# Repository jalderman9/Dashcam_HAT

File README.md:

# Dashcam HAT

This repository contains the Eagle PCB design files for a board that
attaches to an ASUS Tinkerboard and provides:
 - Regulated 5V power from OBD-II 12V supply
 - Power management via Attiny
 - OBD-II interface (CAN and ISO9141)
 - 3 axis accelerometer
 - magnetometer
 - GPS

PCB top view:

PCB bottom view:

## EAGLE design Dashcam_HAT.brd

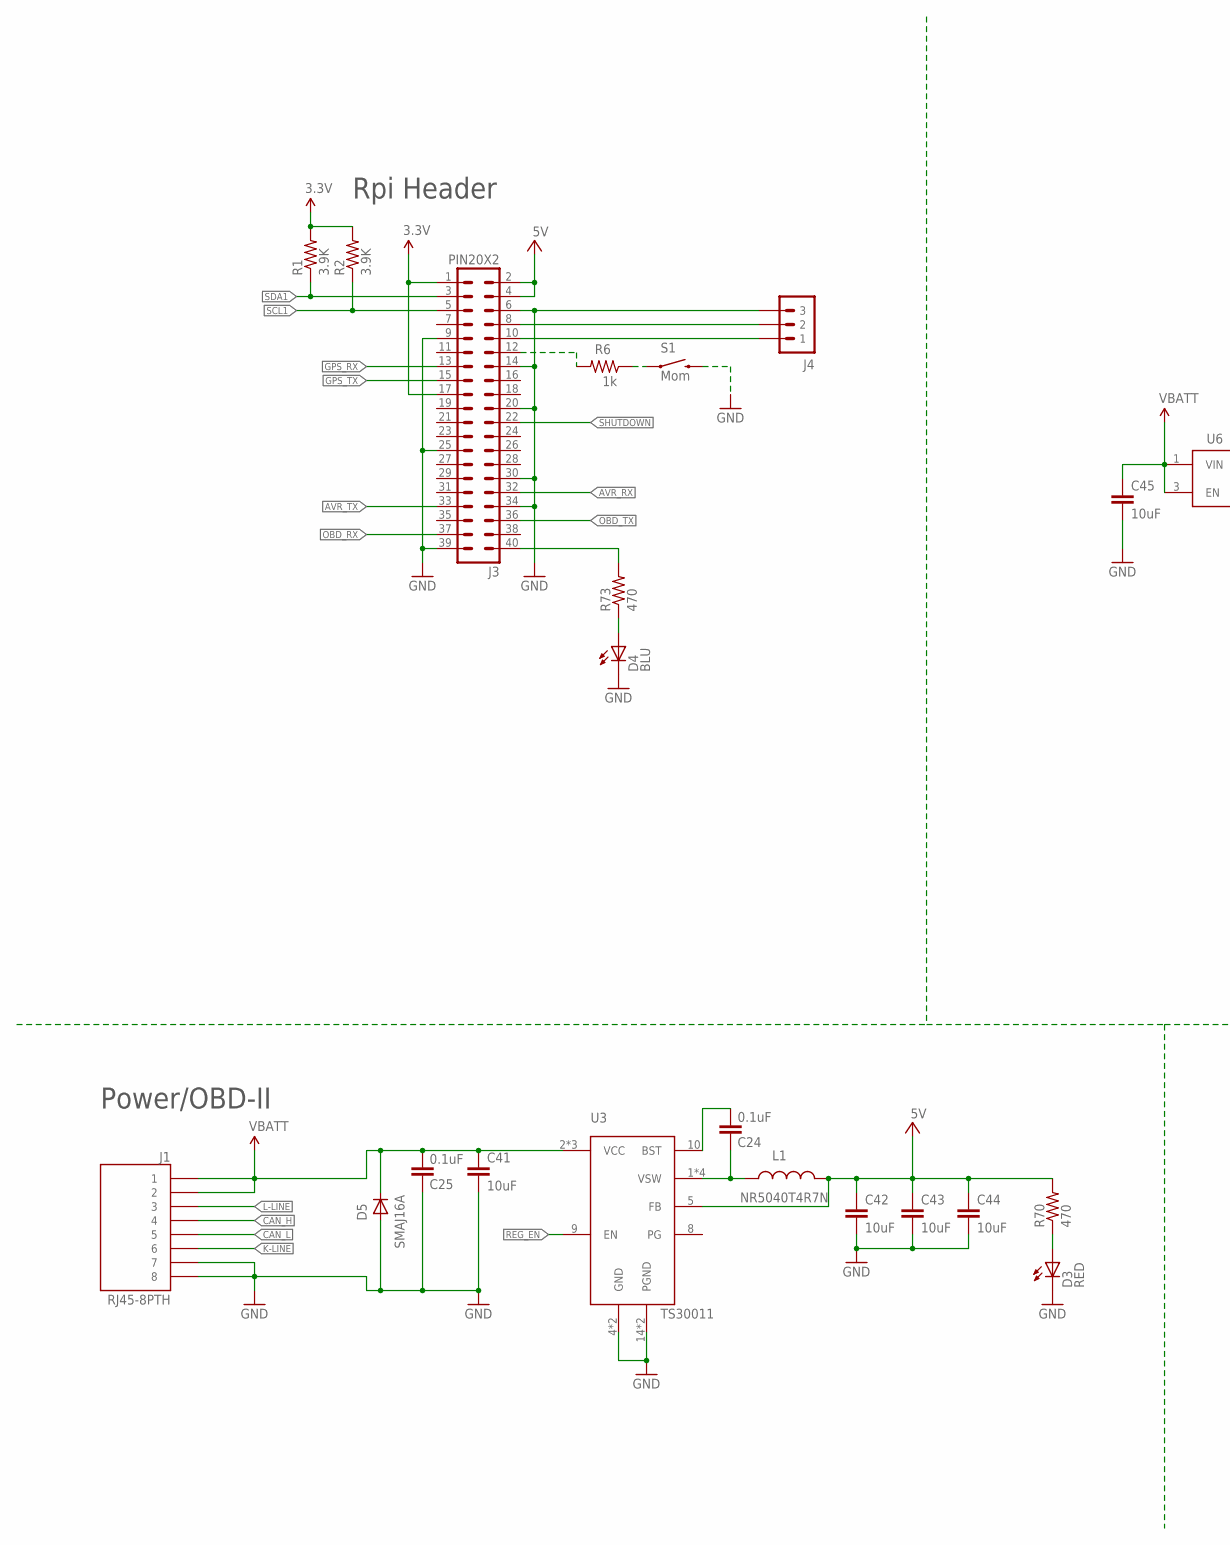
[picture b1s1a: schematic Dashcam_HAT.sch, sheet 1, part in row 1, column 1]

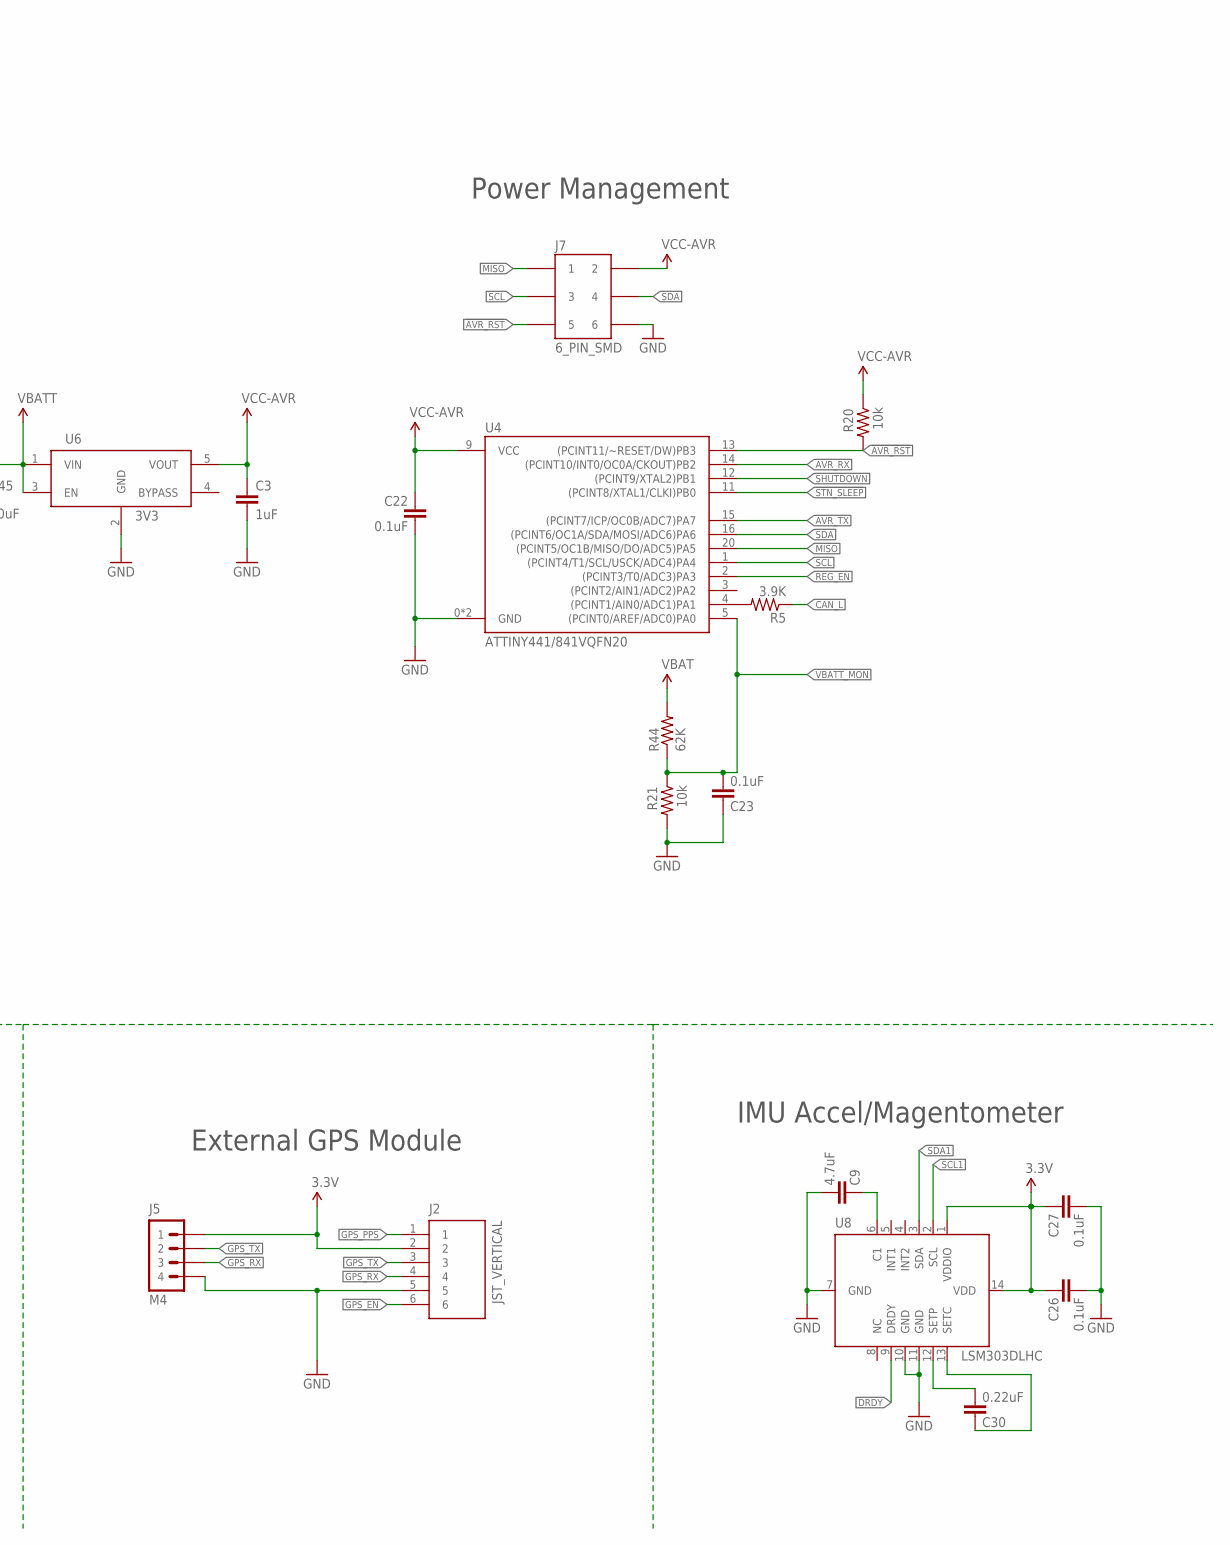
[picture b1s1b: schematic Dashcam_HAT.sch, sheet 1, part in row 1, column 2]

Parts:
C3: 1uF; 0402-CAP; MFG_PN GRM155R61A105KE15D; DIGIKEY_PN 490-3890-1-ND
C9: 4.7uF; 0402-CAP; MFG_PN GRM155R60J475ME47D; DIGIKEY_PN 490-5915-1-ND
C22, C23, C24, C25, C26, C27: 0.1uF; 0402-CAP; MFG_PN CL05B104KO5NNNC; DIGIKEY_PN 1276-1001-1-ND
C30: 0.22uF; 0402-CAP; MFG_PN GRM155R71C224KA12D; DIGIKEY_PN 490-5418-1-ND
C41, C42, C43, C44, C45: 10uF; 1206; MFG_PN CL31B106KBHNNNE; DIGIKEY_PN 1276-6767-1-ND
D3: RED; LED_0603; MFG_PN LTST-C190KRKT; DIGIKEY_PN 160-1436-1-ND
D4: BLU; LED_0603; MFG_PN LTST-C190TBKT; DIGIKEY_PN 160-1646-1-ND
D5: SMAJ16A; SMA; MFG_PN SMAJ16A; DIGIKEY_PN SMAJ16ALFCT-ND
J1: RJ45-8PTH; RJ45-8; MFG_PN 54602-908LF; DIGIKEY_PN 609-1046-ND
J2: JST_VERTICAL; JST-6-SMD-VERT-1.0MM; MFG_PN BM06B-SRSS-TB(LF)(SN); DIGIKEY_PN 455-1792-1-ND
J3: PIN20X2; PIN_20X2; MFG_PN ESQ-120-23-T-D; DIGIKEY_PN SAM9315-ND
J4: M30.1"_LOCK; M3X1_LOCK
J5: M4; M4X1_LOCK
J7: 6_PIN_SMD; M3X2_SMD; MFG_PN 20021121-00006C4LF; DIGIKEY_PN 609-3693-1-ND
L1: NR5040T4R7N; NR5040; MFG_PN 587-2373-1-ND; DIGIKEY_PN 587-2373-1-ND
R1, R2, R5: 3.9K; 0402-RES; MFG_PN RC0402JR-073K9L; DIGIKEY_PN 311-3.9KJRCT-ND
R6: 1k; 0402-RES; MFG_PN RC0402JR-071KL; DIGIKEY_PN 311-1.0KJRCT-ND
R20, R21: 10k; 0402-RES; MFG_PN RC0402JR-0710KL; DIGIKEY_PN 311-10KJRCT-ND
R44: 62K; 0402-RES; MFG_PN RC0402FR-0762KL; DIGIKEY_PN 311-62.0KLRCT-ND
R70, R73: 470; 0603-RES; MFG_PN RC0402JR-07470RL; DIGIKEY_PN 311-470JRCT-ND
S1: Mom; TACTILE-SWITCH-1101NE; MFG_PN EVQ-PNF04M; DIGIKEY_PN P13597SCT-ND
U3: TS30011; QFN-16; MFG_PN TS30013-M050QFNR; DIGIKEY_PN TS30013-M050QFNRCT-ND
U4: ATTINY441/841VQFN20; QFN20_0.45MM; MFG_PN ATTINY841-MMH; DIGIKEY_PN ATTINY841-MMH-ND
U6: 3V3; SOT23-5; MFG_PN AP2204K-3.3TRG1; DIGIKEY_PN AP2204K-3.3TRG1DICT-ND
U8: LSM303DLHC; LGA14; MFG_PN LSM303DLHCTR; DIGIKEY_PN 497-11918-1-ND

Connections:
3.3V: C26.1, C27.1, J2.2, J3.1, J3.17, J5.1, R1.2, R2.2, U8.1 (VDDIO), U8.14 (VDD); also elsewhere on the board
5V: C42.1, C43.1, C44.1, J3.2, J3.4, L1.P$2 (2), R70.2, U3.5 (FB); also elsewhere on the board
!AVR_RST: J7.P$5 (5), R20.2, U4.13 ((PCINT11/~RESET/DW)PB3)
!STN_SLEEP: U4.11 ((PCINT8/XTAL1/CLKI)PB0); also elsewhere on the board
AVR_RX: J3.32, U4.14 ((PCINT10/INT0/OC0A/CKOUT)PB2)
AVR_TX: J3.33, U4.15 ((PCINT7/ICP/OC0B/ADC7)PA7)
BST: C24.2, U3.10 (BST)
CAN_H: J1.4; also elsewhere on the board
CAN_L: J1.5, R5.1; also elsewhere on the board
DRDY: U8.9 (DRDY)
GND: C3.2, C9.2, C22.2, C23.1, C25.1, C26.2, C27.2, C41.2, C42.2, C43.2, C44.2, C45.2, D3.C, D4.C, D5.A, J1.7, J1.8, J2.5, J3.6, J3.9, J3.14, J3.20, J3.25, J3.30, J3.34, J3.39, J4.3, J5.4, J7.P$6 (6), R21.2, S1.P$2 (2), U3.4 (GND), U3.14 (PGND), U3.15 (PGND), U3.EXP (GND), U4.0 (GND), U4.8 (GND), U6.2 (GND), U8.7 (GND), U8.10 (GND), U8.11 (GND); also elsewhere on the board
GPS_EN: J2.6
GPS_PPS: J2.1
GPS_RX: J2.4, J3.13, J5.3
GPS_TX: J2.3, J3.15, J5.2
K-LINE: J1.6; also elsewhere on the board
L-LINE: J1.3; also elsewhere on the board
MISO: J7.P$1 (1), U4.20 ((PCINT5/OC1B/MISO/DO/ADC5)PA5)
unnamed: C9.1, U8.6 (C1)
unnamed: R5.2, U4.4 ((PCINT1/AIN0/ADC1)PA1)
unnamed: D3.A, R70.1
unnamed: D4.A, R73.1
unnamed: C30.2, U8.12 (SETP)
unnamed: C30.1, U8.13 (SETC)
unnamed: J3.12, R6.2
unnamed: R6.1, S1.P$1 (1)
OBD_RX: J3.37; also elsewhere on the board
OBD_TX: J3.36; also elsewhere on the board
REG_EN: U3.9 (EN), U4.2 ((PCINT3/T0/ADC3)PA3)
SCL: J7.P$3 (3), U4.1 ((PCINT4/T1/SCL/USCK/ADC4)PA4)
SCL1: J3.5, R2.1, U8.2 (SCL)
SDA: J7.P$4 (4), U4.16 ((PCINT6/OC1A/SDA/MOSI/ADC6)PA6)
SDA1: J3.3, R1.1, U8.3 (SDA)
SHUTDOWN: J3.22, U4.12 ((PCINT9/XTAL2)PB1)
UART1_RX: J3.10, J4.1
UART1_TX: J3.8, J4.2
USER_LED: J3.40, R73.2
VBATT: C25.2, C41.1, C45.1, D5.K (C), J1.1, J1.2, R44.2, U3.2 (VCC), U3.3 (VCC), U3.11 (VCC), U6.1 (VIN), U6.3 (EN); also elsewhere on the board
VBATT_MON: C23.2, R21.1, R44.1, U4.5 ((PCINT0/AREF/ADC0)PA0)
VCC-AVR: C3.1, C22.1, J7.P$2 (2), R20.1, U4.9 (VCC), U6.5 (VOUT)
VSW: C24.1, L1.P$1 (1), U3.1 (VSW), U3.12 (VSW), U3.13 (VSW), U3.16 (VSW)

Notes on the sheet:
External GPS Module
Rpi Header
IMU Accel/Magentometer
Power/OBD-II
Power Management

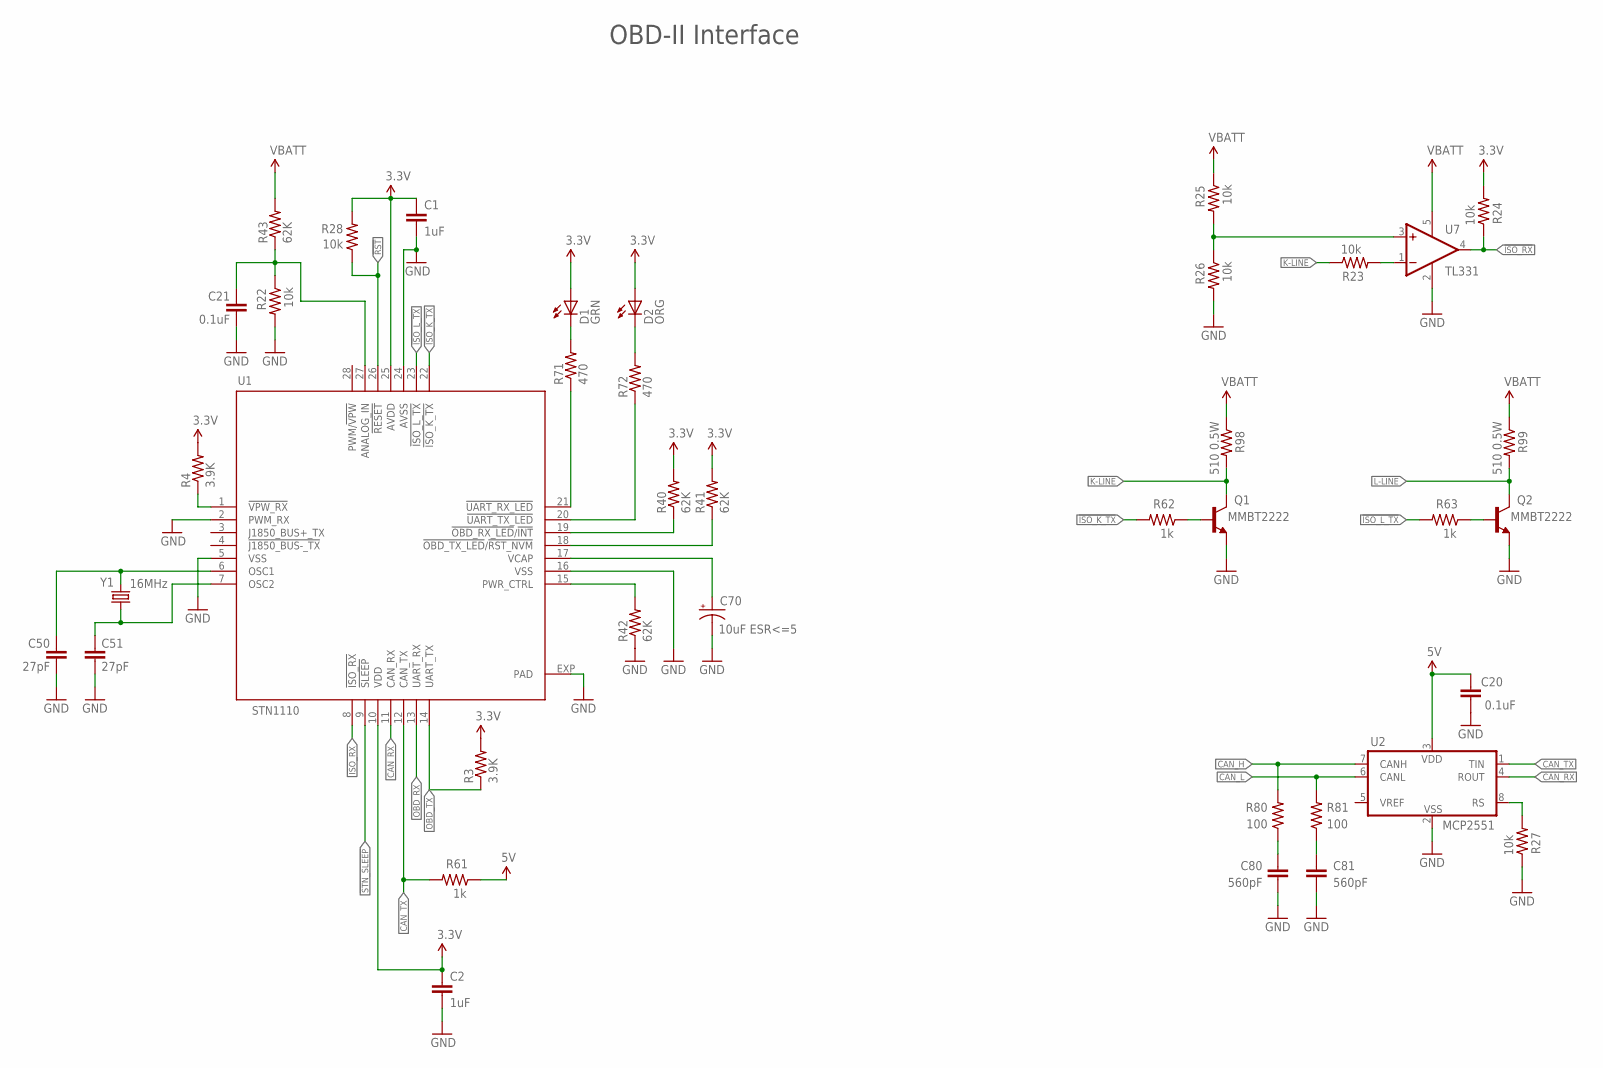
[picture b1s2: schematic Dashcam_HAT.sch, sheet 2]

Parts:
C1, C2: 1uF; 0402-CAP; MFG_PN GRM155R61A105KE15D; DIGIKEY_PN 490-3890-1-ND
C20, C21: 0.1uF; 0402-CAP; MFG_PN CL05B104KO5NNNC; DIGIKEY_PN 1276-1001-1-ND
C50: 27pF; 0402-CAP; MFG_PN CL05C270JB5NNNC; DIGIKEY_PN 1276-1153-1-ND
C51: 27pF; 0402-CAP
C70: 10uF ESR<=5; EIA3216; MFG_PN F931C106MAA; DIGIKEY_PN 478-8237-1-ND
C80, C81: 560pF; 0402-CAP; MFG_PN CL05B561KB5NNNC; DIGIKEY_PN 1276-1577-1-ND
D1: GRN; LED_0603; MFG_PN LTST-C190GKT; DIGIKEY_PN 160-1183-1-ND
D2: ORG; LED_0603; MFG_PN LTST-C190KFKT; DIGIKEY_PN 160-1434-1-ND
Q1, Q2: MMBT2222; SOT23-3; MFG_PN MMBT2222ALT1G; DIGIKEY_PN MMBT2222ALT1GOSCT-ND
R3, R4: 3.9K; 0402-RES; MFG_PN RC0402JR-073K9L; DIGIKEY_PN 311-3.9KJRCT-ND
R22, R23, R24, R25, R26, R27: 10k; 0402-RES; MFG_PN RC0402JR-0710KL; DIGIKEY_PN 311-10KJRCT-ND
R28: 10k; 0402-RES
R40, R41, R42, R43: 62K; 0402-RES; MFG_PN RC0402FR-0762KL; DIGIKEY_PN 311-62.0KLRCT-ND
R61, R62, R63: 1k; 0402-RES; MFG_PN RC0402JR-071KL; DIGIKEY_PN 311-1.0KJRCT-ND
R71, R72: 470; 0603-RES; MFG_PN RC0402JR-07470RL; DIGIKEY_PN 311-470JRCT-ND
R80, R81: 100; 0402-RES; MFG_PN RC0402JR-07100RL; DIGIKEY_PN 311-100JRCT-ND
R98, R99: 510 0.5W; 2010; MFG_PN MCR50JZHJ511; DIGIKEY_PN RHM510BGCT-ND
U1: STN1110; _STN_SCANTOOL_QFN-28-S
U2: MCP2551; SO-8; MFG_PN MCP2551T-E/SN; DIGIKEY_PN MCP2551T-E/SNCT-ND
U7: TL331; DBV-R-PDSO-G5; MFG_PN TL331IDBVR; DIGIKEY_PN 296-10168-1-ND
Y1: 16MHz; CRYSTAL-SMD-5X3; MFG_PN ABM3B-16.000MHZ-B2-T; DIGIKEY_PN 535-9122-1-ND

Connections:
3.3V: C1.1, C2.1, D1.A, D2.A, R3.2, R4.2, R24.2, R28.2, R40.2, R41.2, U1.10 (VDD), U1.25 (AVDD); also elsewhere on the board
5V: C20.1, R61.1, U2.3 (VDD); also elsewhere on the board
!ISO_K_TX: R62.2, U1.22 (!ISO_K_TX)
!ISO_L_TX: R63.2, U1.23 (!ISO_L_TX)
!ISO_RX: R24.1, U1.8 (!ISO_RX), U7.4 (OUT)
!RST: R28.1, U1.26 (!RESET)
!STN_SLEEP: U1.9 (!SLEEP); also elsewhere on the board
BATT_V: C21.1, R22.1, R43.1, U1.27 (ANALOG_IN)
CAN_H: R80.2, U2.7 (CANH); also elsewhere on the board
CAN_L: R81.2, U2.6 (CANL); also elsewhere on the board
CAN_RX: U1.11 (CAN_RX), U2.4 (ROUT)
CAN_TX: R61.2, U1.12 (CAN_TX), U2.1 (TIN)
GND: C1.2, C2.2, C20.2, C21.2, C50.2, C51.2, C70.C (-), C80.2, C81.2, Q1.2 (E), Q2.2 (E), R22.2, R26.2, R27.1, R42.1, U1.2 (PWM_RX), U1.5 (VSS), U1.16 (VSS), U1.24 (AVSS), U1.EXP (PAD), U2.2 (VSS), U7.2 (GND); also elsewhere on the board
K-LINE: Q1.3 (C), R23.1, R98.2; also elsewhere on the board
L-LINE: Q2.3 (C), R99.2; also elsewhere on the board
unnamed: R71.1, U1.21 (!UART_RX_LED)
unnamed: Q1.1 (B), R62.1
unnamed: Q2.1 (B), R63.1
unnamed: R25.2, R26.1, U7.3 (+IN)
unnamed: R72.1, U1.20 (!UART_TX_LED)
unnamed: R42.2, U1.15 (PWR_CTRL)
unnamed: R4.1, U1.1 (!VPW_RX)
unnamed: C80.1, R80.1
unnamed: R27.2, U2.8 (RS)
unnamed: R23.2, U7.1 (-IN)
unnamed: R41.1, U1.18 (!OBD_TX_LED!/!RST_NVM)
unnamed: R40.1, U1.19 (!OBD_RX_LED!/!INT)
unnamed: C70.A (+), U1.17 (VCAP)
unnamed: C81.1, R81.1
unnamed: D1.C, R71.2
unnamed: D2.C, R72.2
OBD_RX: U1.13 (UART_RX); also elsewhere on the board
OBD_TX: R3.1, U1.14 (UART_TX); also elsewhere on the board
OSC1: C50.1, U1.6 (OSC1), Y1.3 (2)
OSC2: C51.1, U1.7 (OSC2), Y1.1
VBATT: R25.1, R43.2, R98.1, R99.1, U7.5 (V+); also elsewhere on the board

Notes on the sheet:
OBD-II Interface

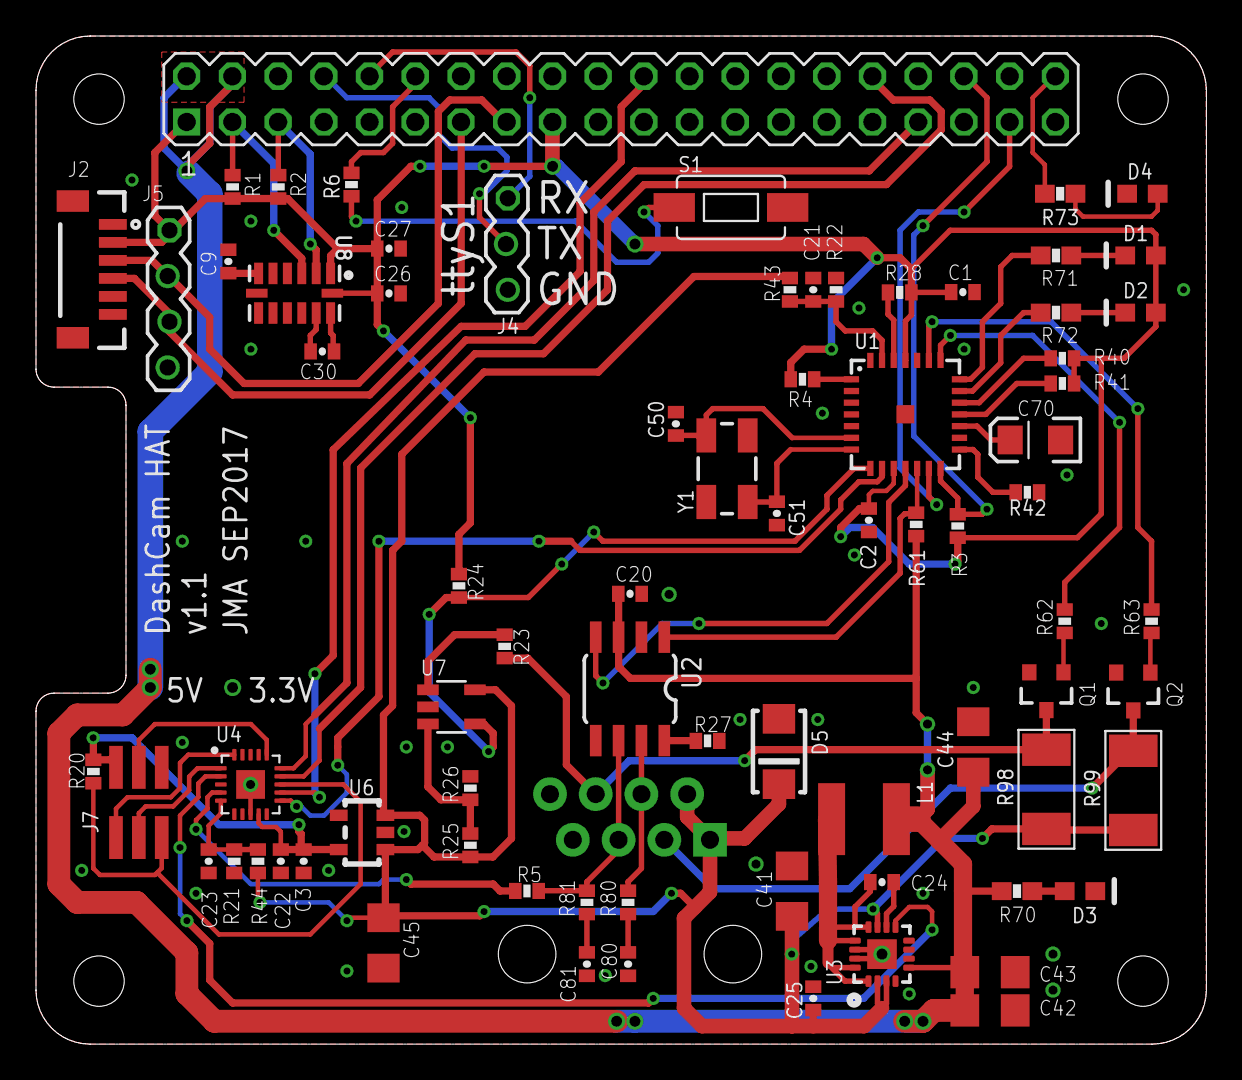
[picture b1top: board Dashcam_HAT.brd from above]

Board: 2 copper layers, 65.0 x 56.0 mm, 77 parts (1 on the bottom side), 63 nets.

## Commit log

2017-09-20 Added missing attributes for TL331 comparator
2017-09-20 Added Bill of Materials
2017-09-20 Added a license file
2017-09-20 Reformatted BOM
2017-09-30 Updated part identifiers
2017-09-30 Tweaked layout a bit and added more bypass caps
2017-10-07 tweaked layout

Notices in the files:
parts and their libraries:
SparkFun-Passives: Licensing: CC v3.0 Share-Alike You are welcome to use this library for commercial purposes.
microbuilder: This work is placed in the public domain, and may be freely used for commercial and non-commercial work with the following conditions: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
